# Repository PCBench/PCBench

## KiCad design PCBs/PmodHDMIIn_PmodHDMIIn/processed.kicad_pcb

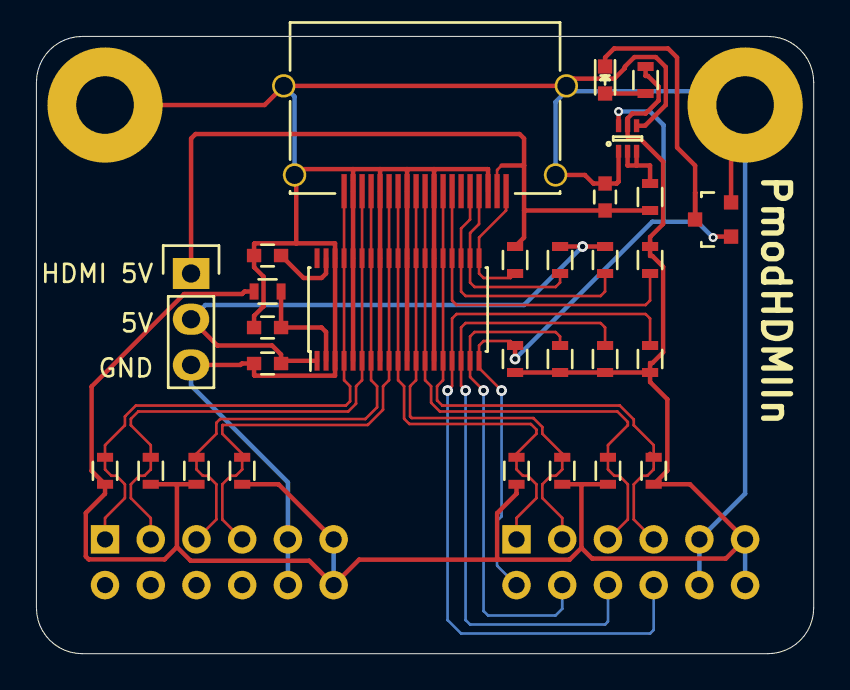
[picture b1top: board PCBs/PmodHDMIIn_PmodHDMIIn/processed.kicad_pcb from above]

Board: 2 copper layers, 43.2 x 34.3 mm, 33 parts (0 on the bottom side), 25 nets.

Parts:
C1, C2, C3: 100n; C_0603
C4: 0u1; C_0603
D1: LED; LED_0603
IC1: TPD12S520DBT; TSSOP-38_4.4x9.7mm_Pitch0.5mm
P1, P2: PMOD; PMOD-DUAL-MALE
P3: HDMI-A; 10029449-11xRLF
P4: POWER; Pin_Header_Straight_1x03
Q1: FDY3000NZ; SOT-563F
Q2: BSS123; SOT-23
R1, R2, R3, R4, R5, R6, R7, R8: 50R; R_0603
R9, R19: 100k; R_0603
R10: 27k; R_0603
R11, R12, R15, R17, R18: 47k; R_0603
R13: 1k; R_0603
R14: 150; R_0603
R16: 10k; R_0603
W1, W2: GND; MountingHole_3-2mm_M3_Pad

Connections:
+3V3: P1.6, P1.12, P2.6, P2.12, Q1.5, R1.1, R2.2, R3.1, R4.2, R5.1, R6.2, R7.1, R8.2, R10.1, R14.1, R15.2, R16.2, R17.2, R18.2, R19.2
+5V: C3.1, IC1.1, P4.2, R11.1, R12.1
/CEC: IC1.16, P2.10, R19.1
/CEC_HDMI: IC1.23, P3.13, R10.2
/HDMI_A_5V: C4.1, P3.18, P4.1, R9.1, R13.1
/HP: IC1.19, P2.7, Q1.6, Q2.1, R15.1
/HP_HDMI: IC1.20, P3.19, R13.2
/SCL: IC1.17, P2.9, R18.1
/SCL_HDMI: IC1.22, P3.15, R11.2
/SDA: IC1.18, P2.8, R17.1
/SDA_HDMI: IC1.21, P3.16, R12.2
/TMDS_0_N: IC1.12, IC1.27, P2.2, P3.9, R6.1
/TMDS_0_P: IC1.10, IC1.29, P2.1, P3.7, R5.2
/TMDS_1_N: IC1.9, IC1.30, P1.4, P3.6, R4.1
/TMDS_1_P: IC1.7, IC1.32, P1.3, P3.4, R3.2
/TMDS_2_N: IC1.6, IC1.33, P1.2, P3.3, R2.1
/TMDS_2_P: IC1.4, IC1.35, P1.1, P3.1, R1.2
/TMDS_C_N: IC1.15, IC1.24, P2.4, P3.12, R8.1
/TMDS_C_P: IC1.13, IC1.26, P2.3, P3.10, R7.2
GND: C1.1, C2.2, C3.2, C4.2, IC1.3, IC1.5, IC1.8, IC1.11, IC1.14, IC1.25, IC1.28, IC1.31, IC1.34, IC1.36, P1.5, P1.11, P2.5, P2.11, P3.2, P3.5, P3.8, P3.11, P3.17, P3.F1, P3.F2, P3.F3, P3.F4, P4.3, Q1.1, Q1.4, Q2.2, W1.1, W2.1
unnamed: C1.2, IC1.37
unnamed: C2.1, IC1.2, R16.1
unnamed: D1.1, Q2.3
unnamed: D1.2, R14.2
unnamed: Q1.2, Q1.3, R9.2

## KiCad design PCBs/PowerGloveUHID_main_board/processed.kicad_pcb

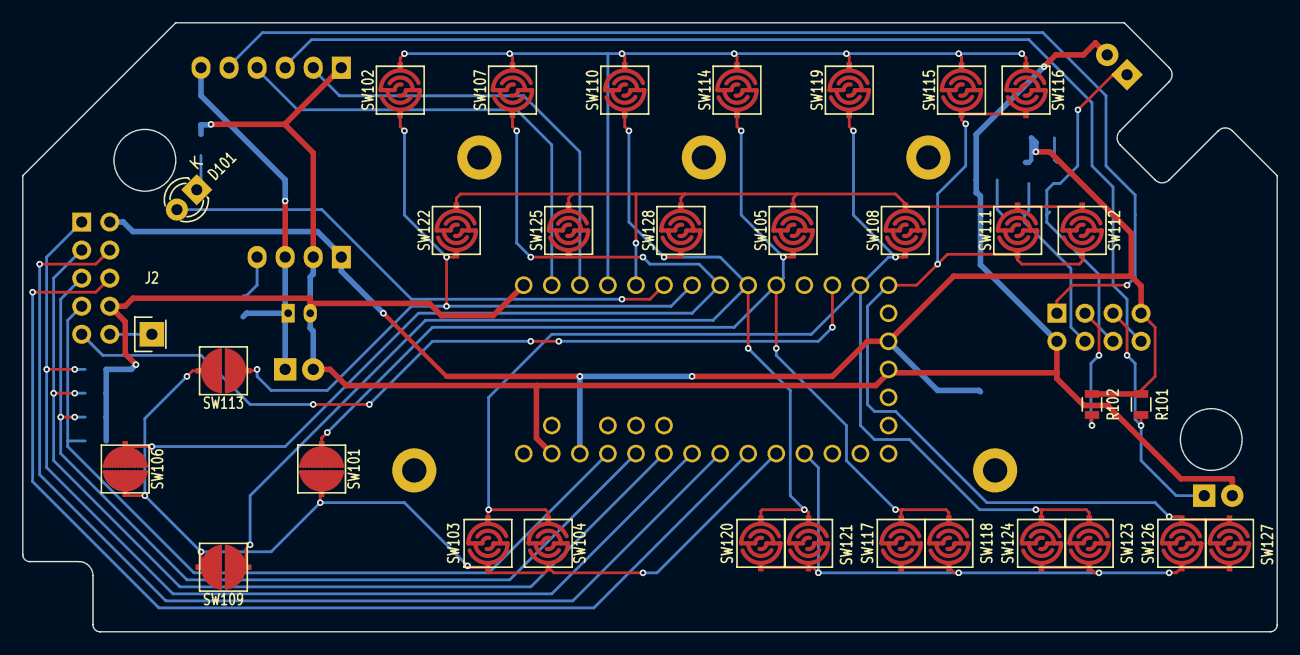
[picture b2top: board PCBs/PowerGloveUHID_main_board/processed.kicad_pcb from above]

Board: 2 copper layers, 113.5 x 55.1 mm, 57 parts (0 on the bottom side), 34 nets.

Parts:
D101: RED; LED-3MM
D102: RED; LED_0805
J1: HEADER_5x2; Socket_Strip_Straight_2x05
J2: HEADER_1; Socket_Strip_Straight_1x01
J104: HEADER_2; Socket_Strip_Straight_1x02
J105: HEADER_4; Socket_Strip_Straight_1x04
J106: HEADER_2; b2b-ph-kl
J108: HEADER_6; Pin_Header_Angled_1x06
M101, M102, M103, M104, M105: MOUNTING-HOLE; MountingHole_2-2mm
R101, R102, R103, R105, R106: 10k; R_0805
R104, R107: 1k; R_0805
R108, R109, R110, R111: 22k; R_0805
SW101, SW106, SW109, SW113: SPST; CONDUCTIVE-PAD-HALFSHELL-150MIL
SW102, SW103, SW104, SW105, SW107, SW108, SW110, SW111, SW112, SW114, SW115, SW116, SW117, SW118, SW119, SW120, SW121, SW122, SW123, SW124, SW125, SW126, SW127, SW128: SPST; CONDUCTIVE-PAD-STANDARD-150MIL
SW129, SW130: SPST; Socket_Strip_Straight_1x02
U1: ESP-01v090; ESP-01
U101: Teensy-LC; Teensy3.x_LC
U102: ESP-12E

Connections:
+3.3V: D102.2, J1.2, J105.1, R101.1, R102.1, R103.1, U1.7, U101.16, U101.31, U102.8
+BATT: J104.1, J105.3, J106.1, J108.6, R106.1
/BUZZER: J1.9, U101.12
/ESP_EN: R102.2, U1.3, U102.3
/ESP_GPIO0: R104.2, SW129.1, U1.6, U102.18
/ESP_GPIO2: R103.2, U1.4, U102.17
/ESP_GPIO15: R105.1, U102.16
/ESP_RESET: R101.2, SW130.1, U1.5, U102.1
/ESP_RX: J108.3, U1.8, U102.21
/ESP_TX: J108.5, U1.1, U102.22
/FLEX1: J1.1, R108.1, U101.27
/FLEX2: J1.3, R109.1, U101.28
/FLEX3: J1.5, R110.1, U101.29
/FLEX4: J1.7, R111.1, U101.30
/I2C_SCL: J1.4, U101.26
/I2C_SDA: J1.6, U101.25
/KM_COL1: SW102.2, SW113.2, SW122.2, U101.7
/KM_COL2: SW106.2, SW107.2, SW125.2, U101.8
/KM_COL3: SW109.2, SW110.2, SW120.2, SW121.2, SW128.2, U101.9
/KM_COL4: SW101.2, SW105.2, SW114.2, SW117.2, SW118.2, U101.10
/KM_COL5: SW103.2, SW104.2, SW108.2, SW119.2, SW123.2, SW124.2, U101.13
/KM_COL6: SW111.2, SW112.2, SW115.2, SW116.2, SW126.2, SW127.2, U101.14
/KM_ROW1: SW102.1, SW107.1, SW110.1, SW114.1, SW115.1, SW116.1, SW119.1, U101.4
/KM_ROW2: SW105.1, SW108.1, SW111.1, SW112.1, SW122.1, SW125.1, SW128.1, U101.5
/KM_ROW3: SW101.1, SW103.1, SW104.1, SW106.1, SW109.1, SW113.1, U101.24
/KM_ROW4: SW117.1, SW118.1, SW120.1, SW121.1, SW123.1, SW124.1, SW126.1, SW127.1, U101.23
/STATUS_LED: D101.2, U101.6
/TEENSY_RX: J108.4, U101.2
/TEENSY_TX: J108.2, U101.3
GND: J1.8, J104.2, J105.2, J106.2, J108.1, R105.2, R107.2, R108.2, R109.2, R110.2, R111.2, SW129.2, SW130.2, U1.2, U101.1, U101.17, U101.32, U102.15
unnamed: D101.1, R107.1
unnamed: D102.1, R104.1
unnamed: J1.10, J2.1
unnamed: J105.4, R106.2

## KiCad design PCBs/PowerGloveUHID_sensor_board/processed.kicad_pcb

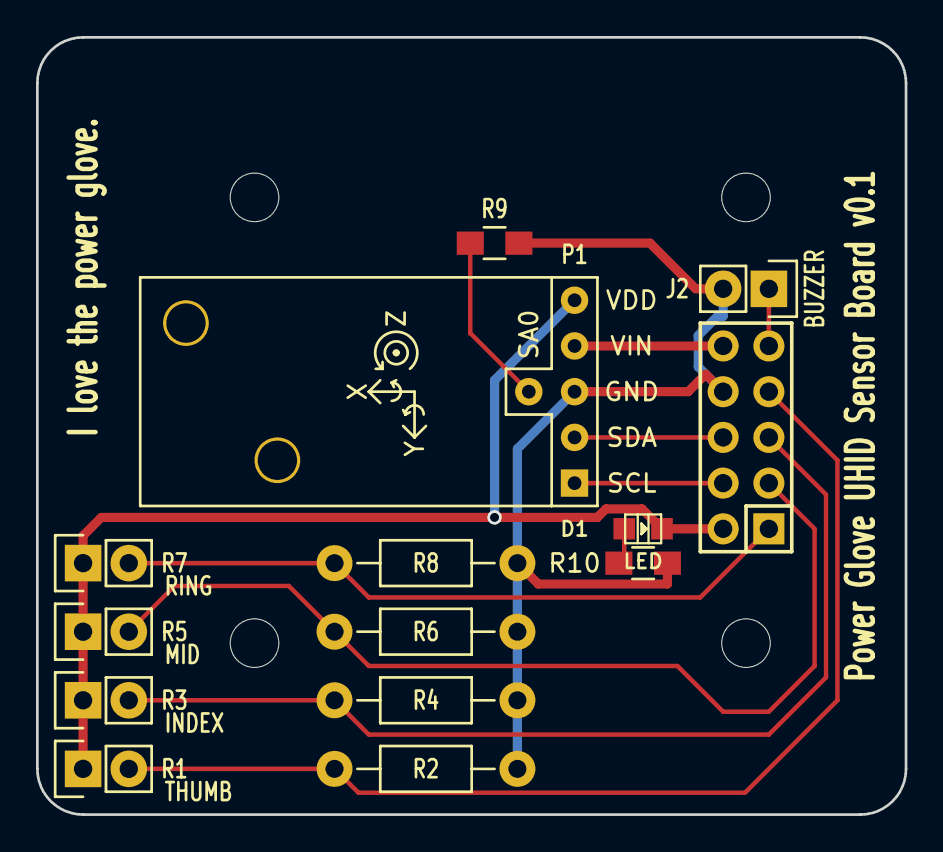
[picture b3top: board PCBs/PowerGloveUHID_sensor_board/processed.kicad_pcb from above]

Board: 2 copper layers, 48.3 x 43.2 mm, 14 parts (1 on the bottom side), 12 nets.

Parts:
D1: LED; Led_0805
J1: HEADER_5x2; Socket_Strip_Straight_2x05
J2: HEADER_2; Socket_Strip_Straight_1x02
P1: CONN_01X06; ALTIMU10
R1, R3, R5, R7: PG_FLEX; Socket_Strip_Straight_1x02
R2, R4, R6, R8: 1M; Resistor_Horizontal_RM10mm
R9: DNP; R_0805_HandSoldering
R10: 1k; R_0805_HandSoldering

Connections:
+3V3: D1.2, J1.2, P1.5, R1.1, R3.1, R5.1, R7.1
/BUZZER: J1.9, J2.1
/FLEX_INDEX: J1.5, R3.2, R4.1
/FLEX_MIDDLE: J1.3, R5.2, R6.1
/FLEX_RING: J1.1, R7.2, R8.1
/FLEX_THUMB: J1.7, R1.2, R2.1
/IMU_SCL: J1.4, P1.1
/IMU_SDA: J1.6, P1.2
/VIN: J1.10, P1.4
GND: J1.8, J2.2, P1.3, R2.2, R4.2, R6.2, R8.2, R9.1, R10.1
unnamed: D1.1, R10.2
unnamed: P1.6, R9.2

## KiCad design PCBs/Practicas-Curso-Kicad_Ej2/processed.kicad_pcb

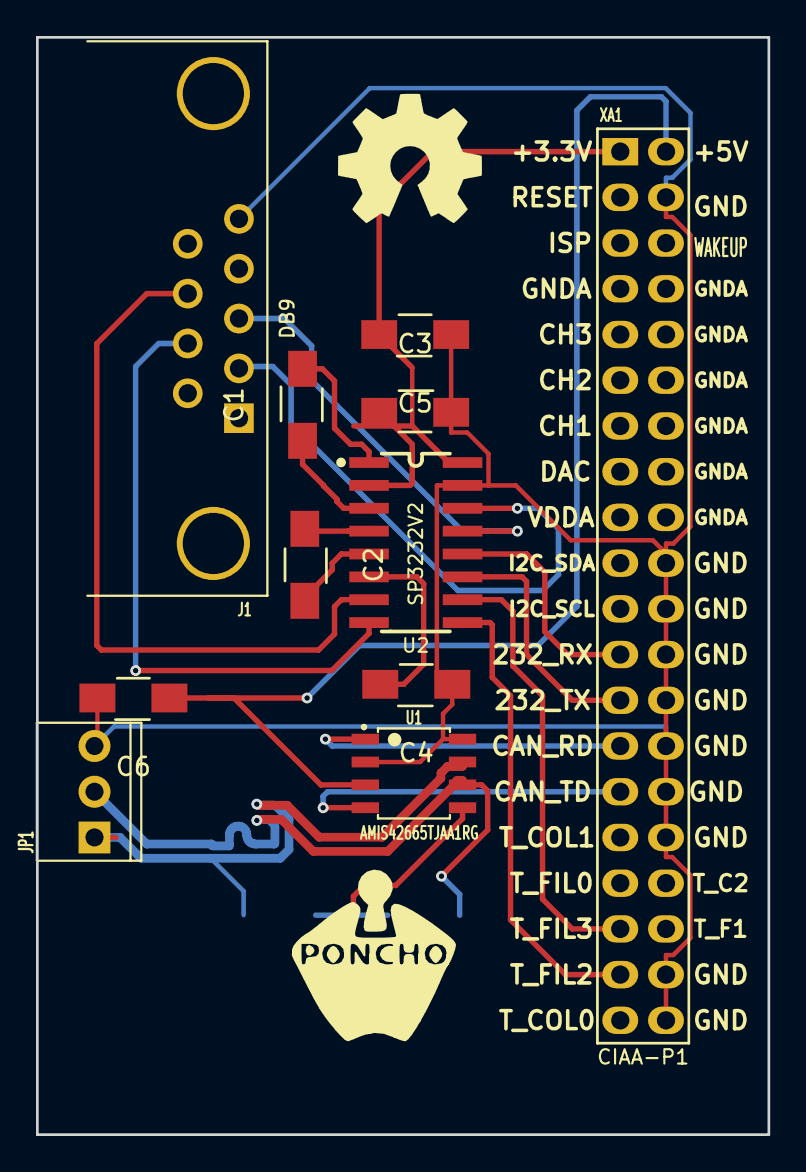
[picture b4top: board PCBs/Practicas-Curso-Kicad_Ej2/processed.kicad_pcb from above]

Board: 2 copper layers, 40.6 x 61.0 mm, 14 parts (0 on the bottom side), 22 nets.

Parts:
C1, C2, C3, C4, C5: C; C_1206_HandSoldering
C6: 100uF; C_1206_HandSoldering
G101: Logo_OSHWA
J1: DB9; DB9_F_TH
JP1: CONN_3; CON_PALETA_3
R1, R2: 60; R_1206_HandSoldering
U1: AMIS42665TJAA1RG; SOIC-8
U2: SP3232V2; SP3232ECN-SOIC16N
XA1: Conn_Poncho2P_2x_20x2; Conn_Poncho_Derecha

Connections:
+3.3V: C5.1, U2.16, XA1.1
+5V: C6.2, U1.3, XA1.2
/conector y can/CAN_N: JP1.2, R2.2, U1.6
/conector y can/CAN_P: JP1.1, R1.1, U1.7
/conector y can/CAN_RX: U1.4, XA1.29
/conector y can/CAN_TX: U1.1, XA1.27
/conector y can/CTS: U2.10, XA1.35
/conector y can/RTS: U2.9, XA1.37
/conector y can/RXD: U2.11, XA1.25
/conector y can/TXD: U2.12, XA1.23
GND: C3.1, C4.2, C5.2, C6.1, J1.5, JP1.3, U1.2, U1.8, U2.15, XA1.4, XA1.20, XA1.22, XA1.24, XA1.26, XA1.28, XA1.30, XA1.32, XA1.38, XA1.40
unnamed: C1.1, U2.1
unnamed: C1.2, U2.3
unnamed: C2.1, U2.5
unnamed: C2.2, U2.4
unnamed: C3.2, U2.2
unnamed: C4.1, U2.6
unnamed: J1.2, U2.14
unnamed: J1.3, U2.13
unnamed: J1.7, U2.8
unnamed: J1.8, U2.7
unnamed: R1.2, R2.1, U1.5

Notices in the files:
PCBs/PmodHDMIIn_PmodHDMIIn/processed.kicad_pcb:
License: CC BY-SA 4.0
